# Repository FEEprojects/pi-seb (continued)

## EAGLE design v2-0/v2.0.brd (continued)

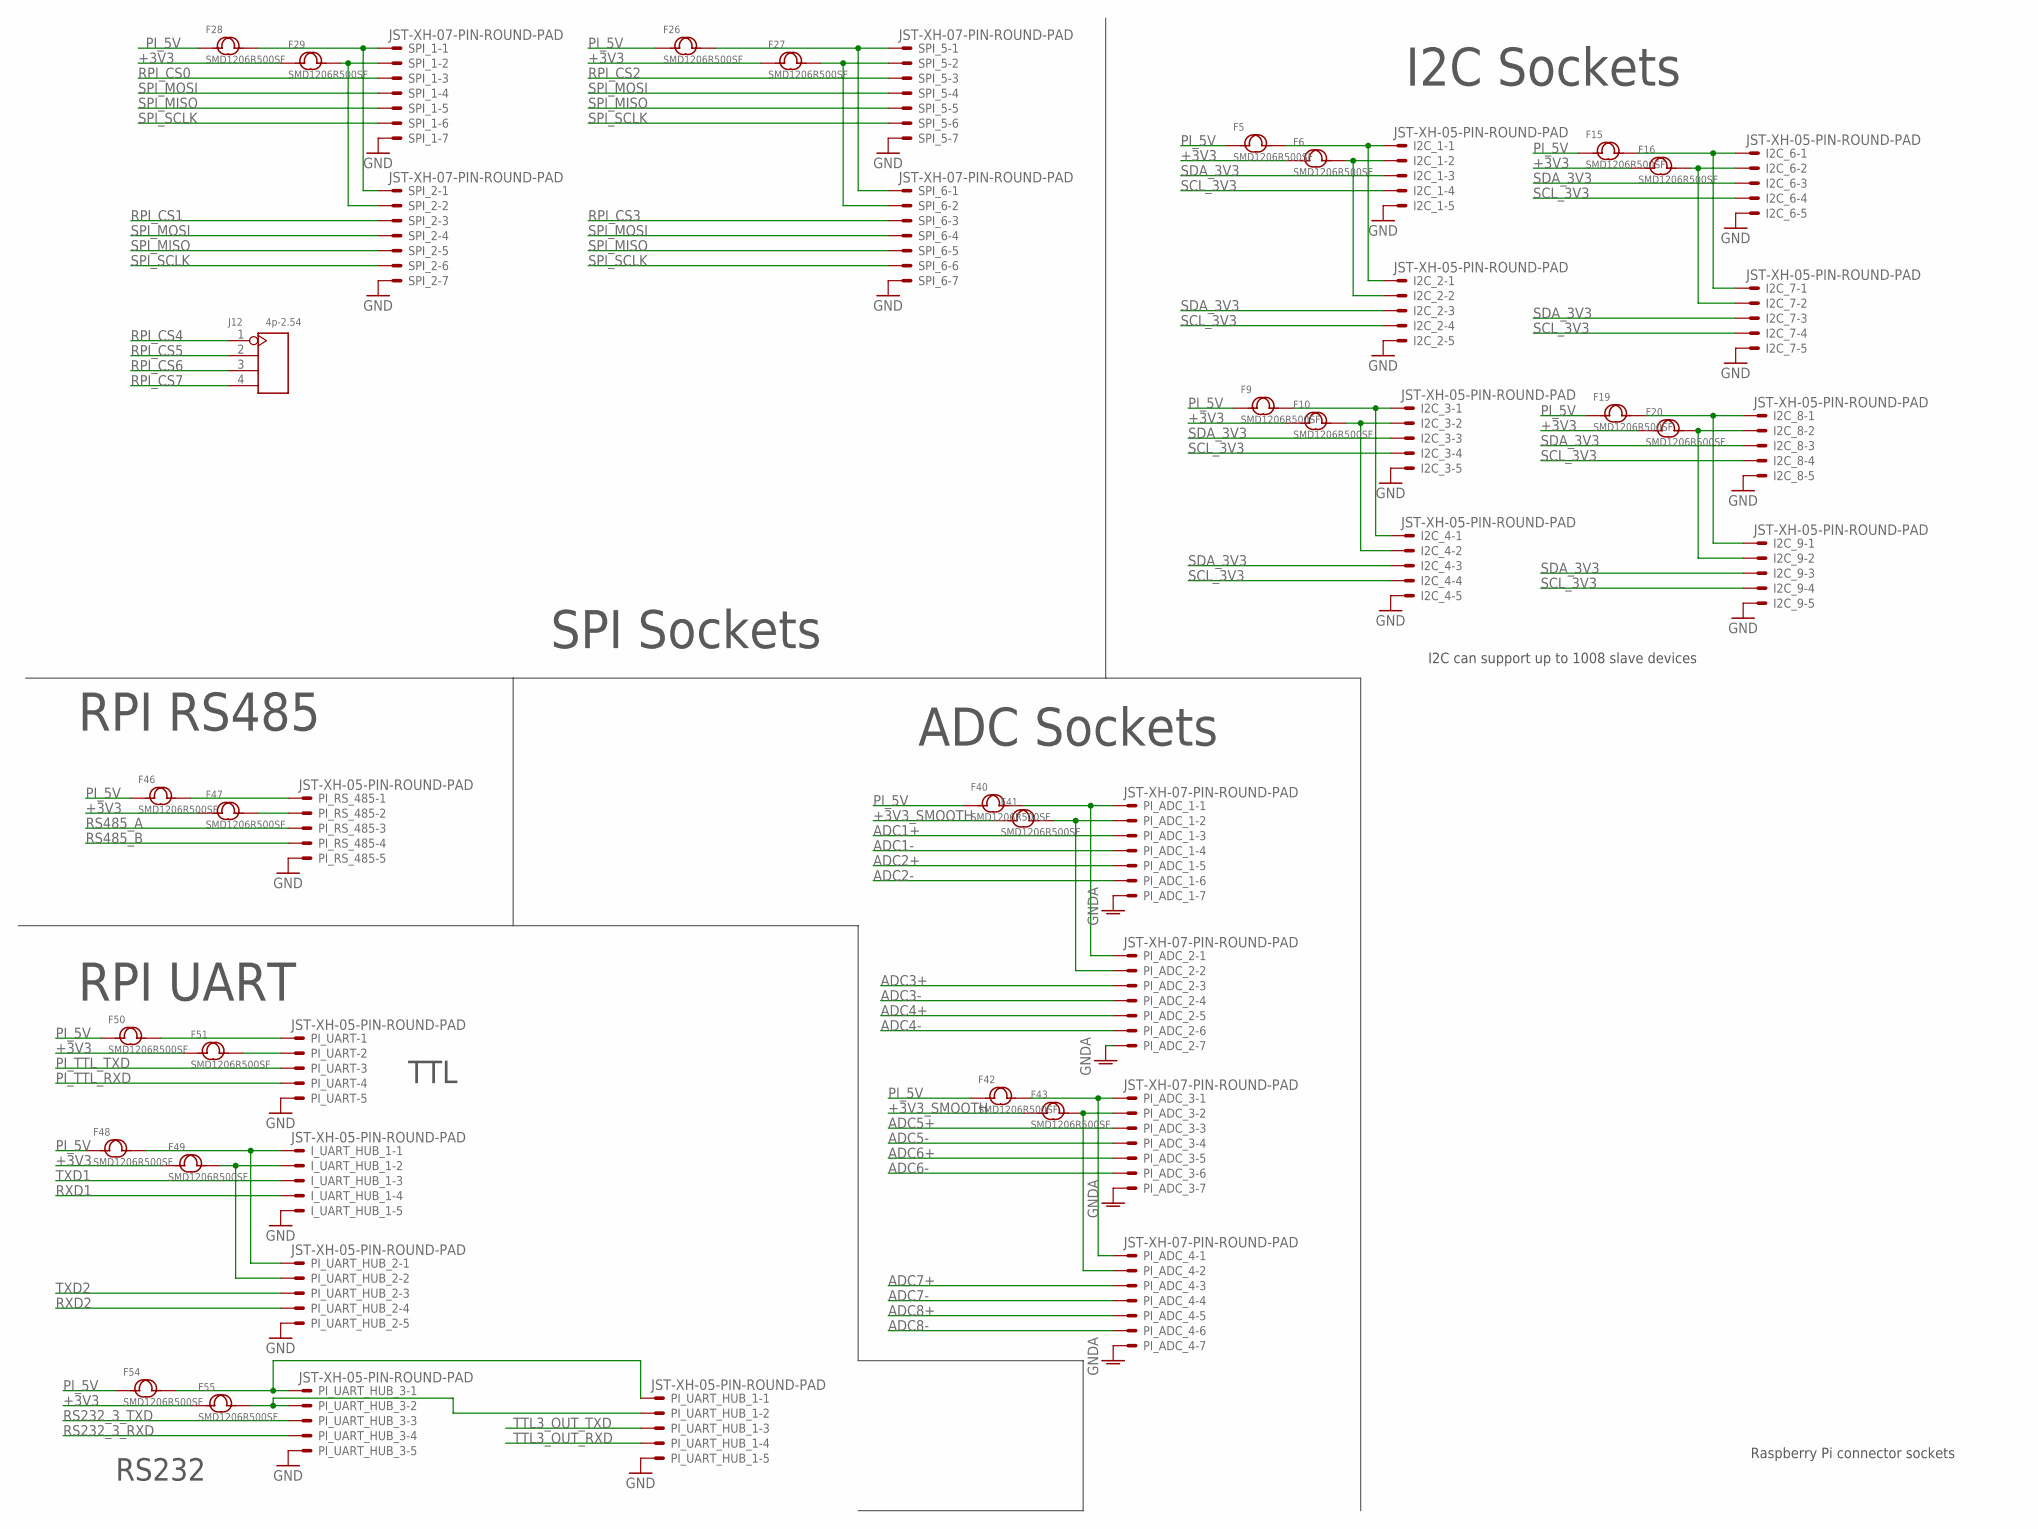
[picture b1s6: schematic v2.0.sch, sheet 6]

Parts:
F5, F6, F9, F10, F15, F16, F19, F20, F26, F27, F28, F29, F40, F41, F42, F43, F46, F47, F48, F49, F50, F51, F54, F55: SMD1206R500SF; F1206
I2C_1, I2C_2, I2C_3, I2C_4, I2C_6, I2C_7, I2C_8, I2C_9: JST-XH-05-PIN-ROUND-PAD; JST-XH-05-PACKAGE-ROUND-PAD
I_UART_HUB_1: JST-XH-05-PIN-ROUND-PAD; JST-XH-05-PACKAGE-ROUND-PAD
J12: 4p-2.54; H4-2.54
PI_ADC_1, PI_ADC_2, PI_ADC_3, PI_ADC_4: JST-XH-07-PIN-ROUND-PAD; JST-XH-07-PACKAGE-ROUND-PAD
PI_RS_485: JST-XH-05-PIN-ROUND-PAD; JST-XH-05-PACKAGE-ROUND-PAD
PI_UART: JST-XH-05-PIN-ROUND-PAD; JST-XH-05-PACKAGE-ROUND-PAD
PI_UART_HUB_1, PI_UART_HUB_2, PI_UART_HUB_3: JST-XH-05-PIN-ROUND-PAD; JST-XH-05-PACKAGE-ROUND-PAD
SPI_1, SPI_2, SPI_5, SPI_6: JST-XH-07-PIN-ROUND-PAD; JST-XH-07-PACKAGE-ROUND-PAD

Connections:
+3V3: F6.1, F10.1, F16.1, F20.1, F27.1, F29.1, F47.1, F49.1, F51.1, F55.1; also elsewhere on the board
+3V3_SMOOTH: F41.1, F43.1; also elsewhere on the board
ADC1+: PI_ADC_1.3; also elsewhere on the board
ADC1-: PI_ADC_1.4; also elsewhere on the board
ADC2+: PI_ADC_1.5; also elsewhere on the board
ADC2-: PI_ADC_1.6; also elsewhere on the board
ADC3+: PI_ADC_2.3; also elsewhere on the board
ADC3-: PI_ADC_2.4; also elsewhere on the board
ADC4+: PI_ADC_2.5; also elsewhere on the board
ADC4-: PI_ADC_2.6; also elsewhere on the board
ADC5+: PI_ADC_3.3; also elsewhere on the board
ADC5-: PI_ADC_3.4; also elsewhere on the board
ADC6+: PI_ADC_3.5; also elsewhere on the board
ADC6-: PI_ADC_3.6; also elsewhere on the board
ADC7+: PI_ADC_4.3; also elsewhere on the board
ADC7-: PI_ADC_4.4; also elsewhere on the board
ADC8+: PI_ADC_4.5; also elsewhere on the board
ADC8-: PI_ADC_4.6; also elsewhere on the board
ADC_1_3V3_P: F41.2, PI_ADC_1.2, PI_ADC_2.2
ADC_1_5V_P: F40.2, PI_ADC_1.1, PI_ADC_2.1
ADC_3_5V_P: F42.2, PI_ADC_3.1, PI_ADC_4.1
ADC_4_3V3_P: F43.2, PI_ADC_3.2, PI_ADC_4.2
GND: I2C_1.5, I2C_2.5, I2C_3.5, I2C_4.5, I2C_6.5, I2C_7.5, I2C_8.5, I2C_9.5, I_UART_HUB_1.5, PI_RS_485.5, PI_UART.5, PI_UART_HUB_1.5, PI_UART_HUB_2.5, PI_UART_HUB_3.5, SPI_1.7, SPI_2.7, SPI_5.7, SPI_6.7; also elsewhere on the board
GNDA: PI_ADC_1.7, PI_ADC_2.7, PI_ADC_3.7, PI_ADC_4.7; also elsewhere on the board
PI_5V: F5.1, F9.1, F15.1, F19.1, F26.1, F28.1, F40.1, F42.1, F46.1, F48.1, F50.1, F54.1; also elsewhere on the board
PI_5V_SPI_1_P: F28.2, SPI_1.1, SPI_2.1
PI_I2C_3V3_2: F10.2, I2C_3.2, I2C_4.2
PI_I2C_3V3_3: F6.2, I2C_1.2, I2C_2.2
PI_I2C_3V3_6: F16.2, I2C_6.2, I2C_7.2
PI_I2C_3V3_8: F20.2, I2C_8.2, I2C_9.2
PI_I2C_5V_P: F5.2, I2C_1.1, I2C_2.1
PI_I2C_5V_P2: F9.2, I2C_3.1, I2C_4.1
PI_I2C_5V_P5: F15.2, I2C_6.1, I2C_7.1
PI_I2C_5V_P7: F19.2, I2C_8.1, I2C_9.1
PI_RS485_3V3_P: F47.2, PI_RS_485.2
PI_RS485_5V_P: F46.2, PI_RS_485.1
PI_SPI_3V3_1_P: F29.2, SPI_1.2, SPI_2.2
PI_TTL_RXD: PI_UART.4; also elsewhere on the board
PI_TTL_TXD: PI_UART.3; also elsewhere on the board
PI_UART_3V3_P: F51.2, PI_UART.2
PI_UART_5V_P: F50.2, PI_UART.1
PI_UART_HUB_1_3V3_P: F49.2, I_UART_HUB_1.2, PI_UART_HUB_2.2
PI_UART_HUB_1_5V_P: F48.2, I_UART_HUB_1.1, PI_UART_HUB_2.1
RPI_CS0: SPI_1.3; also elsewhere on the board
RPI_CS1: SPI_2.3; also elsewhere on the board
RPI_CS2: SPI_5.3; also elsewhere on the board
RPI_CS3: SPI_6.3; also elsewhere on the board
RPI_CS4: J12.1; also elsewhere on the board
RPI_CS5: J12.2; also elsewhere on the board
RPI_CS6: J12.3; also elsewhere on the board
RPI_CS7: J12.4; also elsewhere on the board
RS232_3_RXD: PI_UART_HUB_3.4; also elsewhere on the board
RS232_3_TXD: PI_UART_HUB_3.3; also elsewhere on the board
RS485_A: PI_RS_485.3; also elsewhere on the board
RS485_B: PI_RS_485.4; also elsewhere on the board
RXD1: I_UART_HUB_1.4; also elsewhere on the board
RXD2: PI_UART_HUB_2.4; also elsewhere on the board
SCL_3V3: I2C_1.4, I2C_2.4, I2C_3.4, I2C_4.4, I2C_6.4, I2C_7.4, I2C_8.4, I2C_9.4; also elsewhere on the board
SDA_3V3: I2C_1.3, I2C_2.3, I2C_3.3, I2C_4.3, I2C_6.3, I2C_7.3, I2C_8.3, I2C_9.3; also elsewhere on the board
SPI_3V3_5_P: F27.2, SPI_5.2, SPI_6.2
SPI_5V_5_P: F26.2, SPI_5.1, SPI_6.1
SPI_MISO: SPI_1.5, SPI_2.5, SPI_5.5, SPI_6.5; also elsewhere on the board
SPI_MOSI: SPI_1.4, SPI_2.4, SPI_5.4, SPI_6.4; also elsewhere on the board
SPI_SCLK: SPI_1.6, SPI_2.6, SPI_5.6, SPI_6.6; also elsewhere on the board
TTL3_OUT_RXD: PI_UART_HUB_1.4; also elsewhere on the board
TTL3_OUT_TXD: PI_UART_HUB_1.3; also elsewhere on the board
TXD1: I_UART_HUB_1.3; also elsewhere on the board
TXD2: PI_UART_HUB_2.3; also elsewhere on the board
UART_HUB_3_3V3_P: F55.2, PI_UART_HUB_1.2, PI_UART_HUB_3.2
UART_USB_HUB_3_5V: F54.2, PI_UART_HUB_1.1, PI_UART_HUB_3.1

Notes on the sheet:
Raspberry Pi connector sockets
I2C can support up to 1008 slave devices
ADC Sockets
RPI RS485
RPI UART
I2C Sockets
SPI Sockets
TTL
RS232

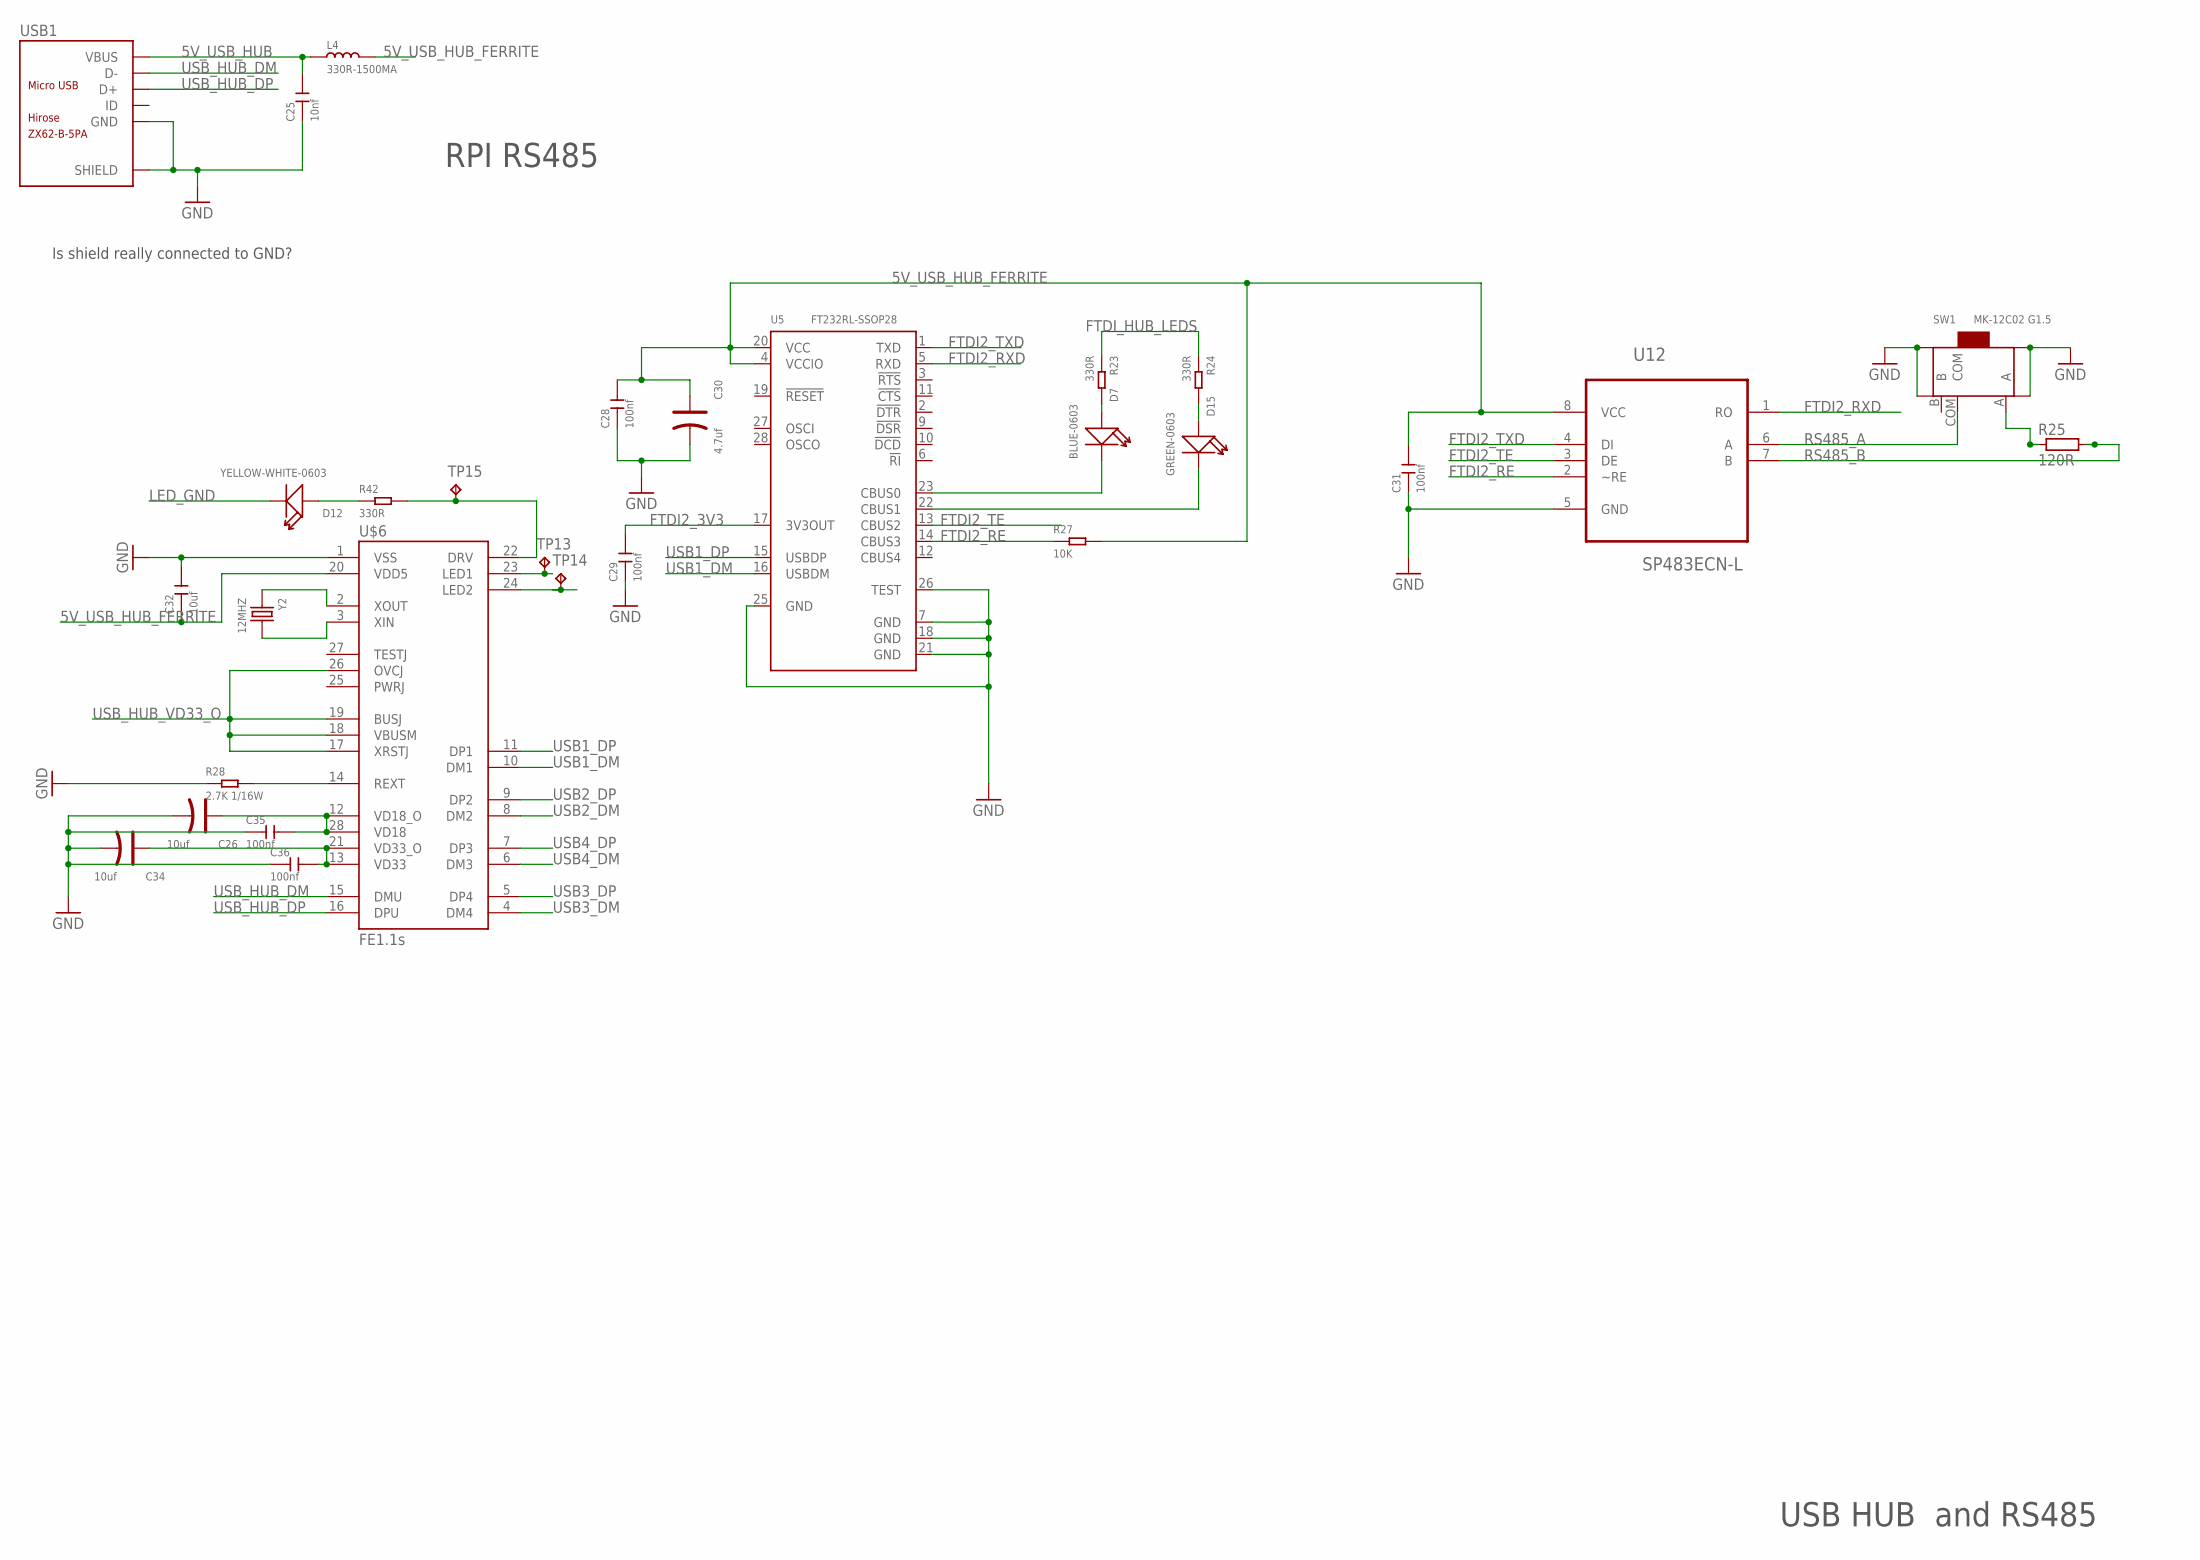
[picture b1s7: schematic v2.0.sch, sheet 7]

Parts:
C25: 10nf; C0603
C26, C34: 10uf; AVX-A
C28, C29, C31, C35, C36: 100nf; C0603
C30: 4.7uf; AVX-A
C32: 10uf; C0805
D7: BLUE-0603; LED-0603
D12: YELLOW-WHITE-0603; LED-0603
D15: GREEN-0603; LED-0603
L4: 330R-1500MA; L0805
R23, R24, R42: 330R; R0603
R25: 120R; R0603
R27: 10K; R0603
R28: 2.7K 1/16W; R0402
SW1: MK-12C02 G1.5; SW7-SMD-L6.7X2.7X3.2MM
TP13, TP14, TP15: TPB2,54; B2,54
U5: FT232RL-SSOP28; SSOP28-0.65-10.2X5.2MM
U12: SP483ECN-L; SOIC127P600X175-8N
U$6: FE1.1S; FE1.1S_SSOP-28
USB1: ZX62-B-5PA; MICRO-USB5+6P-SMD-0.65-AB
Y2: 12MHZ; X2-SMD-5.0X3.2X1.3MM

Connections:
5V_USB_HUB: C25.2, L4.1, USB1.1 (VBUS); also elsewhere on the board
5V_USB_HUB_FERRITE: C28.2, C30.+, C31.2, C32.1, L4.2, R27.2, U5.4 (VCCIO), U5.20 (VCC), U12.8 (VCC), U$6.20 (VDD5); also elsewhere on the board
FTDI2_3V3: C29.2, U5.17 (3V3OUT)
FTDI2_RE: R27.1, U5.14 (CBUS3), U12.2 (~RE)
FTDI2_RXD: U5.5 (RXD), U12.1 (RO)
FTDI2_TE: U5.13 (CBUS2), U12.3 (DE)
FTDI2_TXD: U5.1 (TXD), U12.4 (DI)
FTDI_HUB_LEDS: R23.1, R24.1; also elsewhere on the board
GND: C25.1, C26.-, C28.1, C29.1, C30.-, C31.1, C32.2, C34.-, C35.1, C36.1, R28.1, SW1.SS1, SW1.SS2, SW1.SS3, SW1.SS4, U5.7 (GND), U5.18 (GND), U5.21 (GND), U5.25 (GND), U5.26 (TEST), U12.5 (GND), U$6.1 (VSS), USB1.5 (GND), USB1.P1 (SHIELD), USB1.P2 (SHIELD), USB1.P3 (SHIELD), USB1.P4 (SHIELD), USB1.P5 (SHIELD), USB1.P6 (SHIELD); also elsewhere on the board
LED_GND: D12.-; also elsewhere on the board
unnamed: R25.1, SW1.A
unnamed: D15.+, R24.2
unnamed: D7.+, R23.2
unnamed: D12.+, R42.1
unnamed: U$6.2 (XOUT), Y2.1
unnamed: U$6.3 (XIN), Y2.2
unnamed: R28.2, U$6.14 (REXT)
unnamed: C26.+, C35.2, U$6.12 (VD18_O), U$6.28 (VD18)
unnamed: C34.+, C36.2, U$6.13 (VD33), U$6.21 (VD33_O)
RS485_A: SW1.COM, U12.6 (A); also elsewhere on the board
RS485_B: R25.2, U12.7 (B); also elsewhere on the board
RS485_CBUS0: D7.-, U5.23 (CBUS0)
RS485_CBUS2: D15.-, U5.22 (CBUS1)
USB1_DM: U5.16 (USBDM), U$6.10 (DM1)
USB1_DP: U5.15 (USBDP), U$6.11 (DP1)
USB2_DM: U$6.8 (DM2); also elsewhere on the board
USB2_DP: U$6.9 (DP2); also elsewhere on the board
USB3_DM: U$6.4 (DM4); also elsewhere on the board
USB3_DP: U$6.5 (DP4); also elsewhere on the board
USB4_DM: U$6.6 (DM3); also elsewhere on the board
USB4_DP: U$6.7 (DP3); also elsewhere on the board
USB_HUB_DM: U$6.15 (DMU), USB1.2 (D-)
USB_HUB_DP: U$6.16 (DPU), USB1.3 (D+)
USB_HUB_DRV: R42.2, TP15.TP, U$6.22 (DRV)
USB_HUB_LED1: TP13.TP, U$6.23 (LED1)
USB_HUB_LED2: TP14.TP, U$6.24 (LED2)
USB_HUB_VD33_O: U$6.17 (XRSTJ), U$6.18 (VBUSM), U$6.19 (BUSJ), U$6.26 (OVCJ)

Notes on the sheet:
RPI RS485
USB HUB and RS485
Is shield really connected to GND?

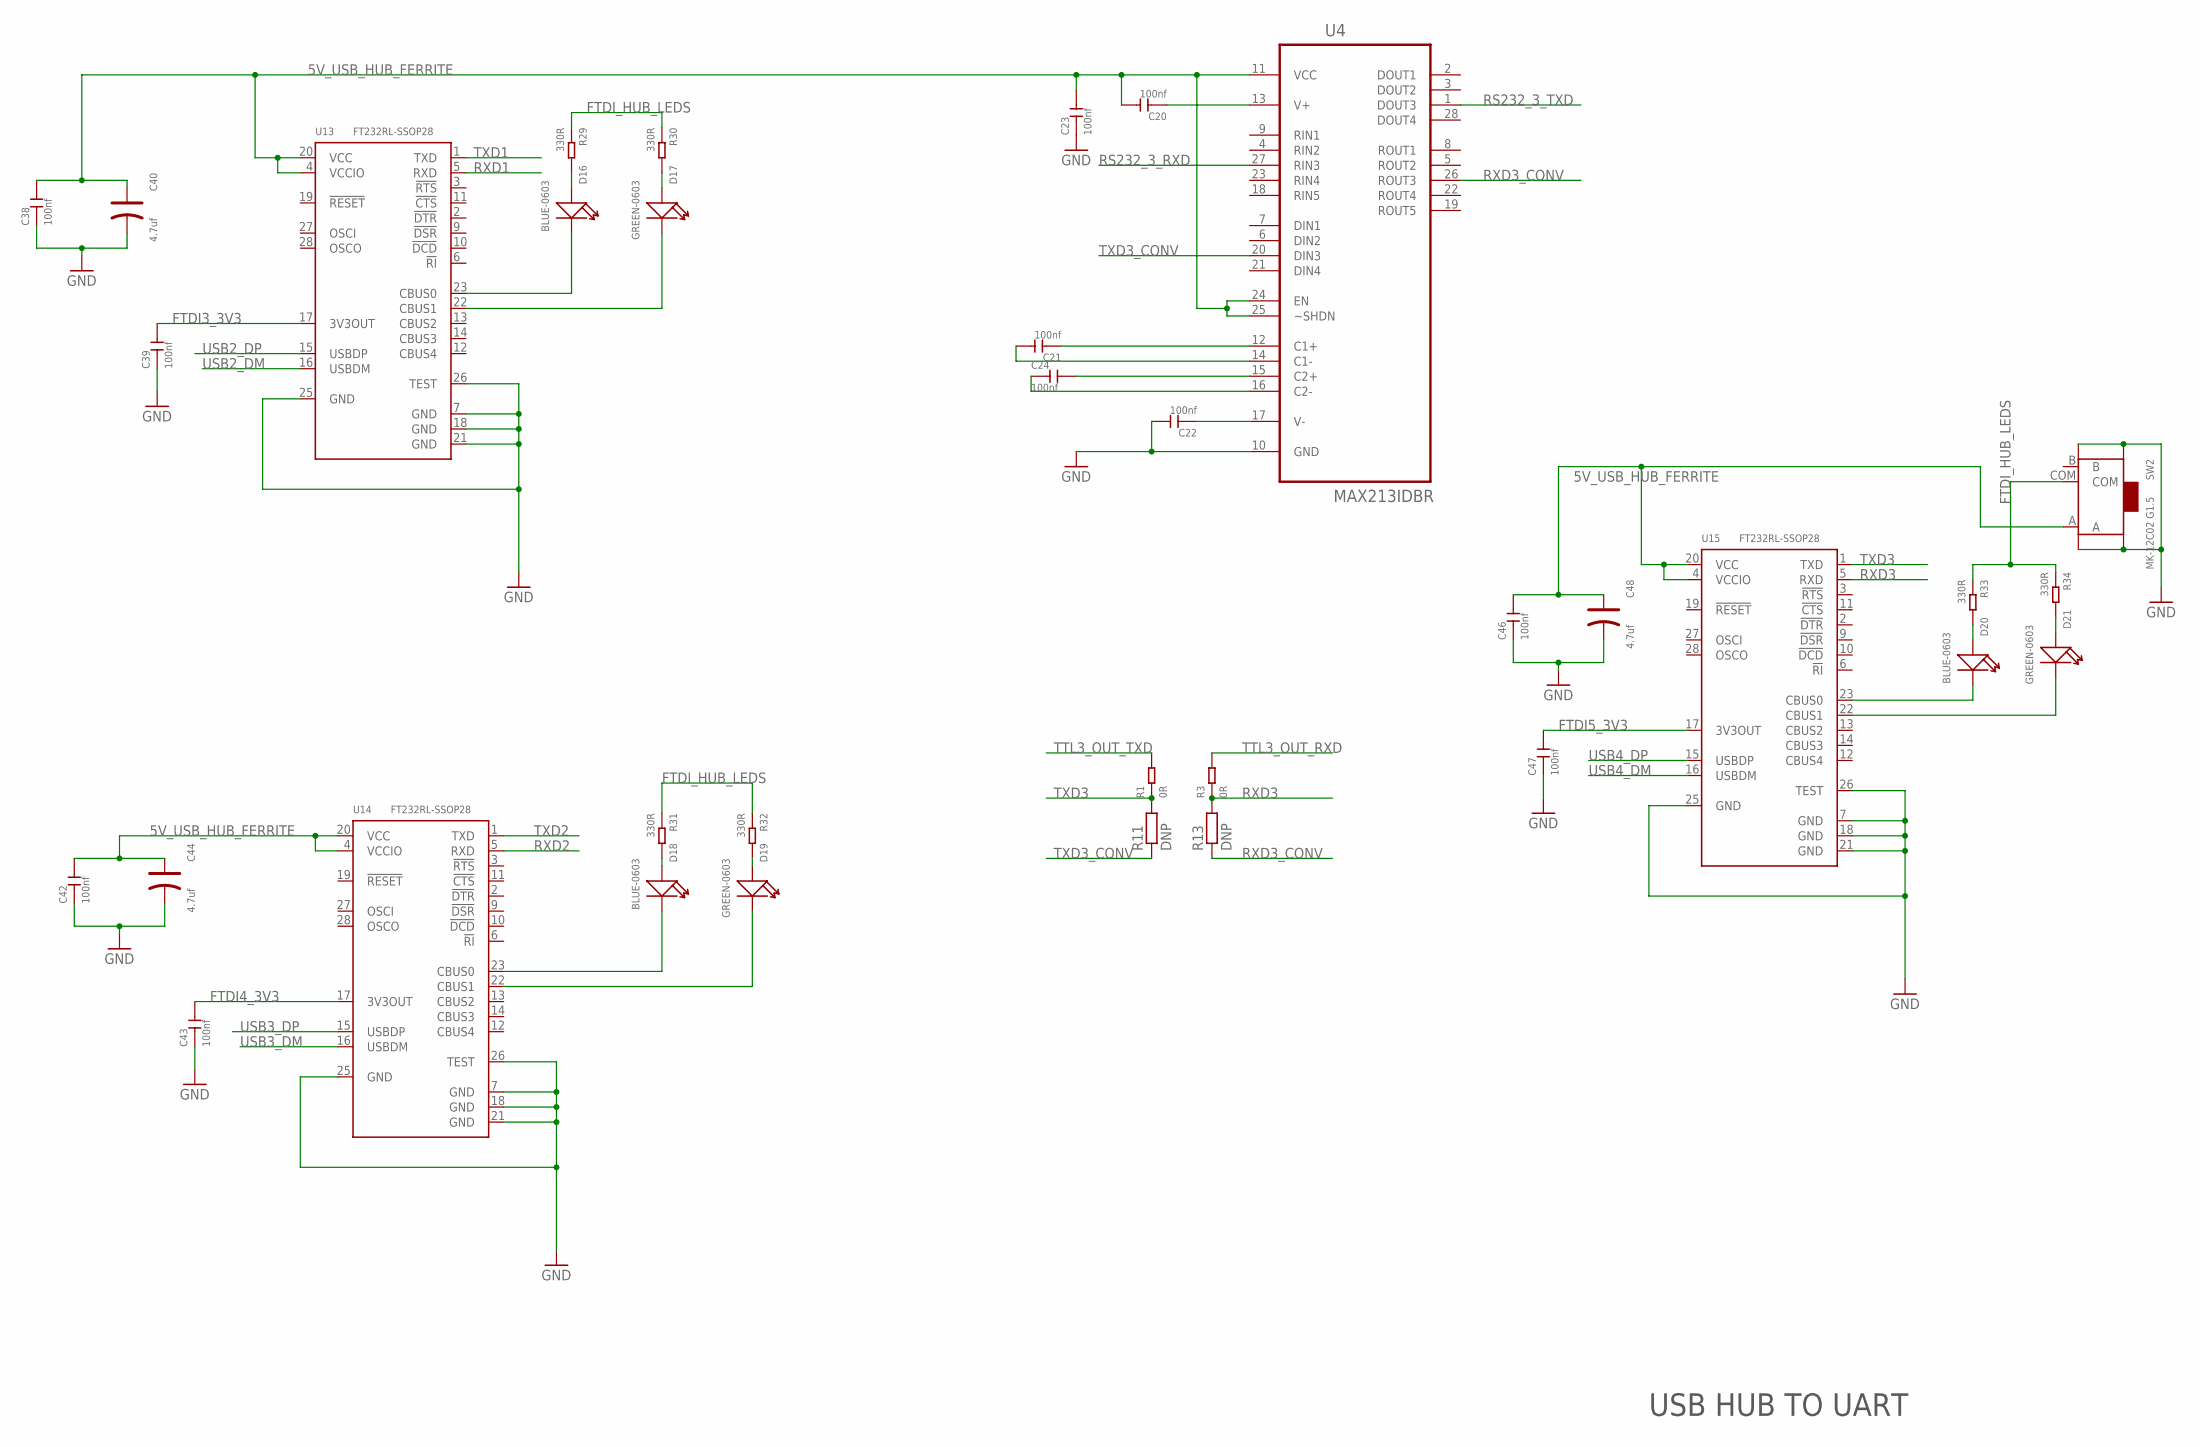
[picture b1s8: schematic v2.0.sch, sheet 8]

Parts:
C20, C21, C22, C23, C24, C38, C39, C42, C43, C46, C47: 100nf; C0603
C40, C44, C48: 4.7uf; AVX-A
D16, D18, D20: BLUE-0603; LED-0603
D17, D19, D21: GREEN-0603; LED-0603
R1, R3: 0R; R0603
R11, R13: DNP; R0603
R29, R30, R31, R32, R33, R34: 330R; R0603
SW2: MK-12C02 G1.5; SW7-SMD-L6.7X2.7X3.2MM
U4: MAX213IDBR; SOP65P780X200-28N
U13, U14, U15: FT232RL-SSOP28; SSOP28-0.65-10.2X5.2MM

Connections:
5V_USB_HUB_FERRITE: C20.2, C23.2, C38.2, C40.+, C42.2, C44.+, C46.2, C48.+, SW2.A, U4.11 (VCC), U4.24 (EN), U4.25 (~SHDN), U13.4 (VCCIO), U13.20 (VCC), U14.4 (VCCIO), U14.20 (VCC), U15.4 (VCCIO), U15.20 (VCC); also elsewhere on the board
FTDI3_3V3: C39.2, U13.17 (3V3OUT)
FTDI4_3V3: C43.2, U14.17 (3V3OUT)
FTDI5_3V3: C47.2, U15.17 (3V3OUT)
FTDI_HUB_LEDS: R29.1, R30.1, R31.1, R32.1, R33.1, R34.1, SW2.COM; also elsewhere on the board
GND: C22.2, C23.1, C38.1, C39.1, C40.-, C42.1, C43.1, C44.-, C46.1, C47.1, C48.-, SW2.SS1, SW2.SS2, SW2.SS3, SW2.SS4, U4.10 (GND), U13.7 (GND), U13.18 (GND), U13.21 (GND), U13.25 (GND), U13.26 (TEST), U14.7 (GND), U14.18 (GND), U14.21 (GND), U14.25 (GND), U14.26 (TEST), U15.7 (GND), U15.18 (GND), U15.21 (GND), U15.25 (GND), U15.26 (TEST); also elsewhere on the board
unnamed: C20.1, U4.13 (V+)
unnamed: C22.1, U4.17 (V-)
unnamed: C21.1, U4.12 (C1+)
unnamed: C21.2, U4.14 (C1-)
unnamed: D20.+, R33.2
unnamed: C24.2, U4.15 (C2+)
unnamed: C24.1, U4.16 (C2-)
unnamed: D21.+, R34.2
unnamed: D16.+, R29.2
unnamed: D17.+, R30.2
unnamed: D18.+, R31.2
unnamed: D19.+, R32.2
RS232_1_LED1: D16.-, U13.23 (CBUS0)
RS232_1_LED2: D17.-, U13.22 (CBUS1)
RS232_2_LED1: D18.-, U14.23 (CBUS0)
RS232_2_LED2: D19.-, U14.22 (CBUS1)
RS232_3_LED1: D20.-, U15.23 (CBUS0)
RS232_3_LED2: D21.-, U15.22 (CBUS1)
RS232_3_RXD: U4.27 (RIN3); also elsewhere on the board
RS232_3_TXD: U4.1 (DOUT3); also elsewhere on the board
RXD1: U13.5 (RXD); also elsewhere on the board
RXD2: U14.5 (RXD); also elsewhere on the board
RXD3: R3.1, R13.2, U15.5 (RXD)
RXD3_CONV: R13.1, U4.26 (ROUT3)
TTL3_OUT_RXD: R3.2; also elsewhere on the board
TTL3_OUT_TXD: R1.2; also elsewhere on the board
TXD1: U13.1 (TXD); also elsewhere on the board
TXD2: U14.1 (TXD); also elsewhere on the board
TXD3: R1.1, R11.2, U15.1 (TXD)
TXD3_CONV: R11.1, U4.20 (DIN3)
USB2_DM: U13.16 (USBDM); also elsewhere on the board
USB2_DP: U13.15 (USBDP); also elsewhere on the board
USB3_DM: U14.16 (USBDM); also elsewhere on the board
USB3_DP: U14.15 (USBDP); also elsewhere on the board
USB4_DM: U15.16 (USBDM); also elsewhere on the board
USB4_DP: U15.15 (USBDP); also elsewhere on the board

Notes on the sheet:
USB HUB TO UART

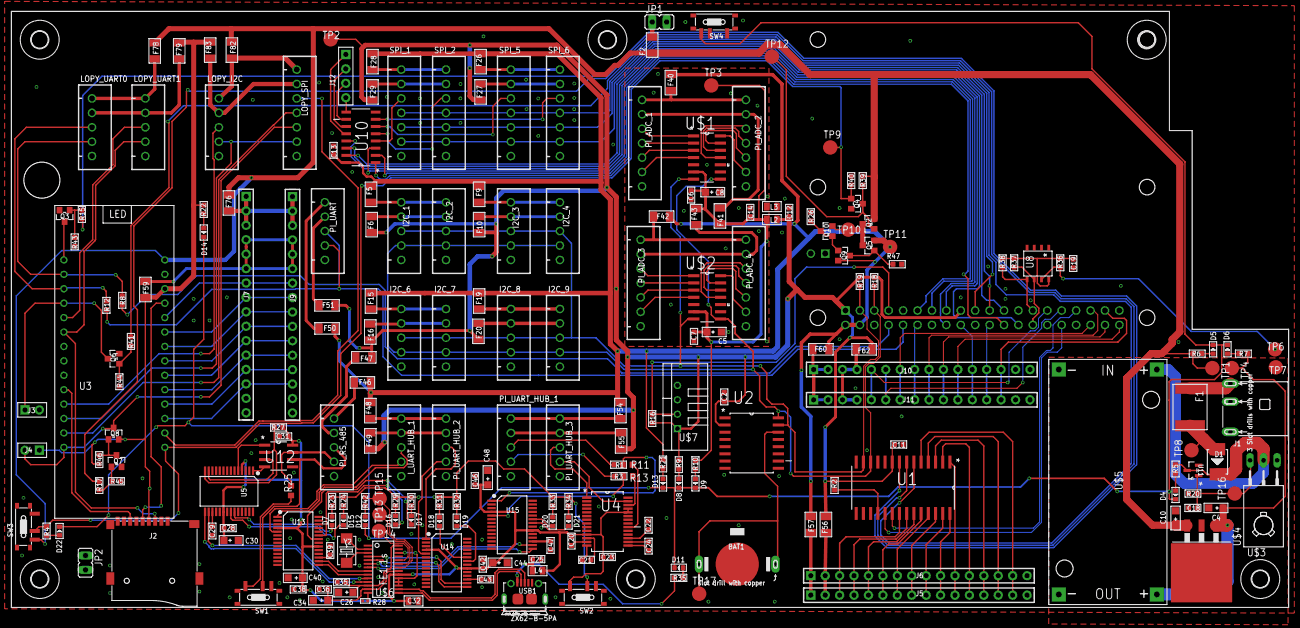
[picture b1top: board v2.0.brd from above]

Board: 2 copper layers, 225.0 x 105.7 mm, 238 parts (1 on the bottom side), 227 nets.

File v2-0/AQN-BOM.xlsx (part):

.Designator | Description | Qty | auto quantity | Value | Source (if not Seeed) | onecall part no | RS part no | Notes | MPN | Min Order (pcs) | Unit Price | Unit Price (£) | Line Total | To Order (pcs) | Order Price | Owned (pcs)
U2 | rtc | 1 | 1 | DS3231SN | http://onecall.farnell.com/maxim-integrated-products/ds3231s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 | 2518948 | 732-7582 |  | DS3231SN# | 1 |  | 8.07 | 8.07 | 16 | 129.12 |  |  |  |  | 1332087 | 16
I2C_1, I2C_2, I2C_3, I2C_4, I2C_6, I2C_7, I2C_8, I2C_9, I_UART_HUB_1, LOPY_I2C,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 |  | 17 | 17 |  | http://uk.rs-online.com/web/p/pcb-headers/8201560/ |  | 820-1560 |  |  | 5 |  | 0.16600000000000001 | 2.8220000000000001 | 260 | 43.160000000000004
LOPY_SPI, PI_ADC_1, PI_ADC_2, PI_ADC_3, PI_ADC_4, SPI_1, SPI_2, SPI_5, SPI_6 |  | 9 | 9 |  | http://uk.rs-online.com/web/p/pcb-headers/8201567/ |  | 820-1567 |  |  | 5 |  | 0.23599999999999999 | 2.1239999999999997 | 140 | 33.04
U10 | spi-mux | 1 | 1 |  | http://onecall.farnell.com/nexperia/74hct139d/74hct-cmos-smd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 | 1085308 |  |  | 74HCT139D | 1 |  | 0.28599999999999998 | 0.28599999999999998 | 16 | 4.5759999999999996
U1 | port expander | 1 | 1 |  | http://uk.farnell.com/microchip/mcp23017-e-so/16bit-expander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 | 1332087 |  |  | MCP23017-E/SO | 1 |  | 1 | 1 | 16 | 16
U11 | zener | 1 | 1 | 30v | http://onecall.farnell.com/multicomp/bzx84c30/diode-zener-0-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 | 1466595 |  |  | BZX84C30 | 5 |  | 4.4999999999999998E-2 | 4.4999999999999998E-2 | 20 | 0.89999999999999991 |  |  |  |  | 1085308 | 16 |  |  | 732-7582 | 16
U$1, U$2 | adc | 2 | 2 |  | http://uk.farnell.com/microchip/mcp3424-e-sl/adc-18bit-quad-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 | 1630424 |  |  | MCP3424-E/SL | 1 |  | 3.41 | 6.82 | 31 | 105.71000000000001 |  |  |  |  | 1466595 | 20 |  |  | 820-1560 | 120
LoPy Header |  | 2 | 1 |  | http://onecall.farnell.com/samtec/ces-114-01-t-s/receptacle-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 | 1667519 |  |  | CES-114-01-T-S | 1 |  | 1.41 | 2.82 | 31 | 43.71 |  |  |  |  | 1593292 | 16 |  |  | 820-1567 | 48
F1 |  | 1 | 1 |  |  | 1822224 |  |  |  | 1 | 9.8000000000000004E-2 | 7.5459999999999999E-2 | 7.5459999999999999E-2 | 16 | 1.20736 |  |  |  |  | 1630424 | 31
U$3 | thyrister | 1 | 1 |  | http://uk.rs-online.com/web/p/thyristors/7743467/ | 2101366 |  |  |  | 10 |  | 0.36199999999999999 | 0.36199999999999999 | 20 | 7.24 |  |  |  |  | 1667519 | 31
RPi Header |  | 1 | 1 |  | http://onecall.farnell.com/samtec/bcs-120-l-d-te/receptacle-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 | 2308433 |  |  | BCS-120-L-D-TE | 1 |  | 5.39 | 5.39 | 16 | 86.24 |  |  |  |  | 1822224 | 16
DCDC Header |  | 4 | 1 |  | http://onecall.farnell.com/wurth-elektronik/61300111121/head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 | 2356152 |  |  | 61300111121 | 1 |  | 5.1999999999999998E-2 | 0.20799999999999999 | 61 | 3.1719999999999997 |  |  |  |  | 2101366 | 20
U8 | eeprom | 1 | 1 |  | http://uk.farnell.com/rohm/br24g32fj-3gte2/serial-eeprom-32k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 | 2373743 |  |  | br24g32-3 | 1 |  | 0.68700000000000006 | 0.68700000000000006 | 16 | 10.992000000000001 |  |  |  |  | 2308433 | 16
U4 | 232 driver | 1 | 1 |  | http://uk.farnell.com/texas-instruments/max213idbr/line-driv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 | 2395902 |  |  | MAX213IDBR | 1 |  | 1.5 | 1.5 | 16 | 24 |  |  |  |  | 2356152 | 61
U$4 | ldo | 1 | 1 |  | http://uk.farnell.com/microchip/mic29300-5-0wu/ldo-volt-reg-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 | 2510021 |  |  |  | 1 |  | 2.85 | 2.85 | 16 | 45.6 |  |  |  |  | 2373743 | 16
R25 |  | 1 | 1 | 120R | Onecall Part No | 9238379 |  |  |  | 10 |  | 1.35E-2 | 1.35E-2 | 20 | 0.27 |  |  |  |  | 2395902 | 16
U12 | rs485 driver | 1 | 1 |  | http://uk.farnell.com/exar/sp483ecn-l/transceiver-rs485-smd-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 | 9387129 |  |  | SP483ECN-L | 1 |  | 1.46 | 1.46 | 16 | 23.36 |  |  |  |  | 2510021 | 16
JP1, JP2 | JUMPER | 2 | 2 |  | http://onecall.farnell.com/harwin/m20-9990246/0-1-pin-header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 | CN09983 |  |  | M20-9990246 | 10 |  | 6.5000000000000002E-2 | 0.13 | 40 | 2.6 |  |  |  |  | 9238379 | 20
BAT1 | 320170002 | 1 | 1 |  |  |  |  |  |  | 1 | 0.01 | 7.7000000000000002E-3 | 7.7000000000000002E-3 | 16 | 0.1232 |  |  |  |  | 9387129 | 16
C2, C6, C7, C11, C12, C13, C14, C18, C19, C20, C21, C22, C23, C24, C28, C29, C3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 | 302010138 | 25 | 25 | 100nF |  |  |  |  | CC0603KRX7R9BB104 | 1 | 0.01 | 7.7000000000000002E-3 | 0.1925 | 376 | 2.8952 |  |  |  |  | CN09983 | 40
C25 | 302010140 | 1 | 1 | 10nF |  |  |  |  | CC0603KRX7R9BB103 | 1 | 0.01 | 7.7000000000000002E-3 | 7.7000000000000002E-3 | 16 | 0.1232
C26, C34 | 302020002 | 2 | 2 | 10uF POL |  |  |  |  | TAJA106K016RNJ | 1 | 4.8000000000000001E-2 | 3.696E-2 | 7.392E-2 | 31 | 1.1457599999999999
C30, C40, C44, C48 | 302020006 | 4 | 4 | 4.7uF POL |  |  |  |  | TAJA475*016#NJ | 1 | 4.1000000000000002E-2 | 3.1570000000000001E-2 | 0.12628 | 61 | 1.92577
C32 | 302010178 | 1 | 1 | 10uF |  |  |  |  | CC0805KKX5R8BB106 | 1 | 1.4999999999999999E-2 | 1.155E-2 | 1.155E-2 | 16 | 0.18479999999999999
C4, C5, C8, C10 | 302020011 | 4 | 4 | 10uF POL |  |  |  |  | TAJA106K010RNJ | 1 | 4.1000000000000002E-2 | 3.1570000000000001E-2 | 0.12628 | 61 | 1.92577
D1 | 304020021 | 1 | 1 | 28V 5A diode |  |  |  |  | SS54B | 1 | 0.104 | 8.0079999999999998E-2 | 8.0079999999999998E-2 | 16 | 1.28128
D12 | 304090071 | 1 | 1 | Yellow LED |  |  |  |  | ADL-0603W | 1 | 4.8000000000000001E-2 | 3.696E-2 | 3.696E-2 | 16 | 0.59136
D15, D17, D19, D21 | 304090043 | 4 | 4 | green LED |  |  |  |  | 19-217-G7C-AN1P2-3T | 1 | 1.4E-2 | 1.078E-2 | 4.3119999999999999E-2 | 61 | 0.65757999999999994
D4, D5, D6, D8, D9, D13, D14, D22 | 304090042 | 8 | 8 | red LED |  |  |  |  | 19-217-R6C-AL1M2VY-3T | 1 | 1.4E-2 | 1.078E-2 | 8.6239999999999997E-2 | 121 | 1.3043799999999999
D7, D11, D16, D18, D20 | 304090045 | 5 | 5 | blue LED |  |  |  |  | 19-217-BHC-ZL1M2RY-3T | 1 | 1.4E-2 | 1.078E-2 | 5.3899999999999997E-2 | 76 | 0.81928000000000001
F2, F5, F6, F9, F10, F15, F16, F19, F20, F26, F27, F28, F29, F40, F41, F42, F43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 | 307010002 | 35 | 35 |  |  |  |  |  | SMD1206R500SF | 1 | 4.7E-2 | 3.619E-2 | 1.2666500000000001 | 526 | 19.03594
H1, H2, H3, H4, H5, H6 |  | 6 | 6 |  |  |  |  | Hole drilled through PCB |  |  |  |  |  |  | -
J1 | 320120002 | 1 | 1 | DC In |  |  |  |  | JACK-DC-044-A | 1 | 9.0999999999999998E-2 | 7.0069999999999993E-2 | 7.0069999999999993E-2 | 16 | 1.1211199999999999
J12 | 320030017 | 1 | 1 | 4p-2.54 |  |  |  |  | F185-1104A1BSYA1 | 1 | 2.1000000000000001E-2 | 1.617E-2 | 1.617E-2 | 16 | 0.25872000000000001
J2 | 320090008 | 1 | 1 | micro SD |  |  |  |  |  | 1 | 0.109 | 8.3930000000000005E-2 | 8.3930000000000005E-2 | 16 | 1.3428800000000001
J3, J4 | 320020016 | 2 | 2 | 2 way male header |  |  |  |  | P125-1102A0BS116A1 | 1 | 0.01 | 7.7000000000000002E-3 | 1.54E-2 | 31 | 0.2387
J5, J6, J7, J9, J10, J11 | 320020034 | 6 | 6 | 16 way header |  |  |  |  | P125-1116A0BS116AX | 1 | 2.5000000000000001E-2 | 1.9250000000000003E-2 | 0.11550000000000002 | 91 | 1.7517500000000004
L2, L3, L4 | 303030006 | 3 | 3 | 330R 1500mA |  |  |  |  | BLM21PG331SN1D | 1 | 1.4999999999999999E-2 | 1.155E-2 | 3.465E-2 | 46 | 0.53129999999999999
PCB1 |  | 1 | 1 |  | http://onecall.farnell.com/raspberry-pi/raspberrypi-modb-1gb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 |  |  | Raspberry Pi |  | 1 | 42.22 | 32.509399999999999 | 32.509399999999999 | 16 | 520.15039999999999
Q2, Q5 | 305030075 | 2 | 2 | ssm3j328r |  |  |  |  | SSM3J328R,LF | 1 | 0.13600000000000001 | 0.10472000000000001 | 0.20944000000000002 | 31 | 3.2463200000000003
Q3, Q4, Q6, Q7 | 305030000 | 4 | 4 | BSS138 |  |  |  |  | BSS138W-7-F | 1 | 3.3000000000000002E-2 | 2.5410000000000002E-2 | 0.10164000000000001 | 61 | 1.5500100000000001
Q8 | 305030014 | 1 | 1 | CJ2305 |  |  |  |  |  | 1 | 3.3000000000000002E-2 | 2.5410000000000002E-2 | 2.5410000000000002E-2 | 16 | 0.40656000000000003
Q9, Q10 | 305020006 | 2 | 2 | S8550 |  |  |  |  |  | 1 | 1.0999999999999999E-2 | 8.4700000000000001E-3 | 1.694E-2 | 31 | 0.26257000000000003
R2, R16, R18, R19, R26, R27 | 301010299 | 6 | 6 | 10k |  |  |  |  | RC0603FR-0710KL | 1 | 0.01 | 7.7000000000000002E-3 | 4.6200000000000005E-2 | 91 | 0.70069999999999999
R20 | 301010241 | 1 | 1 | 15k |  |  |  |  | RC0603FR-0715KL | 1 | 0.01 | 7.7000000000000002E-3 | 7.7000000000000002E-3 | 16 | 0.1232
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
